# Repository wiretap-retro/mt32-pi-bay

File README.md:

# mt32-pi-bay
A 5.25" bay panel overlay to control the mt32-pi. 
\
\

## Info
The core project design is attributed to Dale Whinham and his awesome mt32-pi project. Repo link: https://github.com/dwhinham/mt32-pi
\
\
This PCB I designed is a 5.25" bay front panel overlay to control the mt32-pi system. It features a power LED, 1.3" OLED, two push buttons, rotary encoder knob, MIDI input jack, and a 3.5mm headphone output jack.
\
\
I have included the full KiCad project along with the Mouser Cart, BOM, and Gerber files for ease of upload.
\
\
This is designed for use with my mt32-pi-zero-breakout project found here: https://github.com/wiretap-retro/mt32-pi-zero-breakout/
\
\
Both the breakout board and 5.25 bay are 100% tested and functional. 

## Parts
The parts in the BOM and Mouser Cart are for building a blue illuminated unit. You can choose other color illuminated components, however you will need to change the resistors to different values since the forward voltage of the LED will be different. Regardless, you should calculate the LED resistors for your desired current/brightness based on the product datasheet curves. The BOM as-is makes the buttons look great, however the power LED is a little bright and could use a slightly higher resistor value.
\
\
Please read the original mt32-pi repository linked in the information section for compatibility of parts if you fork the design or deviate from the chosen parts.

## Assembly
- First solder all the components to the board. To keep the screen low-profile, no pin header socket should be used.
- Solder your wire pigtails to the DIN connector and 3.5mm connector.
- Next, insert the DIN and 3.5mm receptacles into the panel and secure them with the lock nuts.
- Test fit the assembled PCB to the StarTech bay adapter. There are going to be slight interferences from the solder fillets sticking out. Trim the bay adapter with a rotary tool or your preferred cutting method. 
- Clean the StarTech bay panel face and rear side of the PCB with isopropyl alcohol.
- Smear a thin layer of silicone caulk on the StarTech bay panel face.
- Set the PCB onto the bay panel face and apply a small amount of force to allow the caulk to spread and adhere. Shift it around to align it with the edges if necessary. 
- Allow a dry time of 24hrs so the PCB fully cures to the bay adapter face.
- Mount your mt32-pi into the StarTech bay adapter and connect the 2.54mm pitch DuPont connectors to the panel header.

## 1U Case and Parts (optional)
- Athena Power 1U Short-Depth Server Chassis with 5.25" Bay - http://athenapower.com/product/ipc-rackmount-chassis/1u-itx-rackmount/rm-1uc138 (other 1U models may work as well)
- Canakit 3.5A Power Supply - https://www.amazon.com/dp/B07TYQRXTK
- IEC320 Power Connector - https://www.amazon.com/dp/B085BQ3NWD
- SPST Blue Rocker Switch - https://www.amazon.com/dp/B08YN7Z9Y3
- 5V Blue Fans - https://www.amazon.com/dp/B084RCBSBX
- USB to 5V Fan Adapter - https://www.amazon.com/dp/B09HGLN7CX
- USB to DuPont Interal Connectors - https://www.ebay.com/itm/391937393112
- 3D Printable IEC to Flex-ATX adapter - https://www.thingiverse.com/thing:7041659
- 3D Printable Canakit Power Supply Enclosure - https://www.thingiverse.com/thing:7052683

## Finished Product

\

\

\

\

\
## Revision Notes
Rev 1 2025-05-28 --- Remapped rotary encoder CW/CCW pins for proper volume up/down when physically turned. \
Rev 0 2025-05-03 --- Cleaned up assembly instructions, added knob to other BOM items section.

## License
This project uses the UNLICENSE. Feel free to do what you want with it. Check over the project before ordering. Build at your own risk.

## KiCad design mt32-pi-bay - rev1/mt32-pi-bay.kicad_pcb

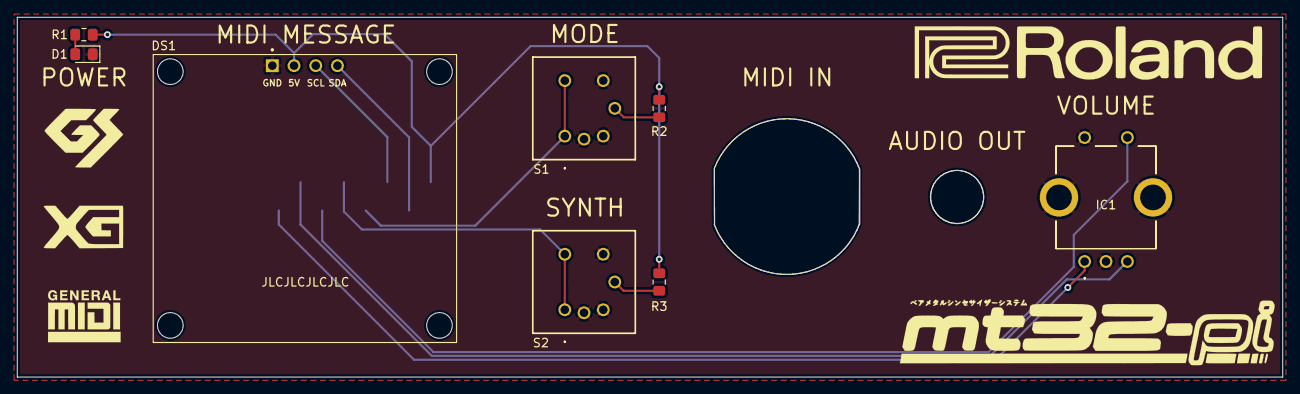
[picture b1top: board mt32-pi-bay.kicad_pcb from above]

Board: 2 copper layers, 148.1 x 42.1 mm, 11 parts (1 on the bottom side), 12 nets.

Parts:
CON1: Same_Sky_SD-LS_DIN5
CON2: Schurter_PG12
D1: LED_Small; LED_0805_2012Metric_Pad1.15x1.40mm_HandSolder
DS1: OLED_128X64_1.3_I2C; LCD_OLED_128X64_1.3_I2C
IC1: EC11E18244A5
J1: Main Header; PinHeader_1x09_P2.54mm_Vertical_SMD_Pin1Right
R1, R2, R3: R_Small; R_0805_2012Metric_Pad1.15x1.40mm_HandSolder
S1, S2: B3W-9010-R1N; B3W9010R1N

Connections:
+5V: DS1.2, J1.1, R1.2, R2.1, R3.1
BTN1: J1.4, S1.1, S1.2
BTN2: J1.5, S2.1, S2.2
ENC_BTN: IC1.E1, J1.6
ENC_CLK: IC1.B1, J1.7
ENC_DAT: IC1.A1, J1.8
GND: D1.1, DS1.1, IC1.C1, IC1.D1, IC1.MH1, IC1.MH2, J1.9, S1.3, S1.4, S1.6, S2.3, S2.4, S2.6
unnamed: D1.2, R1.1
unnamed: R2.2, S1.5
unnamed: R3.2, S2.5
SCL: DS1.3, J1.3
SDA: DS1.4, J1.2

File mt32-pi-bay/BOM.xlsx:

mt32-pi 5.25" Bay Device (BLUE LEDs)
Reference | Quantity | Value | Footprint | Description | Manufacturer Name | Part Number | Notes
D1 | 1 | LED_Small | LED_SMD:LED_0805_2012Metric_Pad1.15x1.40mm_HandSolder | 0805 SMD Blue LED | VCC | LSM0805463V | In Mouser Cart
DS1 | 1 | OLED_128X64_1.3_I2C | SamacSys_Parts:LCD_OLED_128X64_1.3_I2C | diymore 1.3" OLED i2c SSH1106 Display | diymore.cc | SKU: 030514LA | Purchase from Ebay/Amazon
IC1 | 1 | EC11E18244A5 | EC11E18244A5 | Encoders 11mm 18 RES 36 DTENT | ALPS Electric | EC11E18244A5 | In Mouser Cart
J1 | 1 | Main Header | Connector_PinHeader_2.54mm:PinHeader_1x09_P2.54mm_Vertical_SMD_Pin1Right | 1x09 2.54mm Pitch SMD Pin Header | Samtec | TSM-109-01-L-SV | In Mouser Cart
R2, R3 | 2 | R_Small | Resistor_SMD:R_0805_2012Metric_Pad1.15x1.40mm_HandSolder | 0805 SMD 75-ohm Resistors | Wurth | 560112120005 | In Mouser Cart
R1 | 1 | R_Small | Resistor_SMD:R_0805_2012Metric_Pad1.15x1.40mm_HandSolder | 0805 SMD 200-ohm Resistors | Wurth | 560112120015 | In Mouser Cart
S1, S2 | 2 | B3W-9010-R1N | B3W9010R1N | Tactile Switches 1 LED RED MILKY WHITE CAP | Omron Electronics | B3W-9010-R1N | In Mouser Cart
MIDI IN | 1 | N/A | Hole | Panel Mount Circular 5P DIN Jack, Female | Same Sky | SD-50LS | In Mouser Cart
AUDIO OUT | 1 | N/A | Hole | Panel Mount 3.5mm TRS Jack, Female | Schurter | 4832.2300 | In Mouser Cart
Mouser Cart Link: | Link
Other:
Bay Adapter | 1ea | StarTech BRACKETFDBK | Source from Amazon, Ebay, and many other computer stores
Silicone Caulk | 1ea | Clear, small tube | Source from Home Depot, Lowes, Amazon, etc.

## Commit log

2025-05-03 Update README.md
    Update readme to make instructions clear.
2025-05-28 Delete mt32-pi-bay directory
    Delete rev0
